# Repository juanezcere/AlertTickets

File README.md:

# AlertTickets
A PCB design to show information about tickets in BCD displays

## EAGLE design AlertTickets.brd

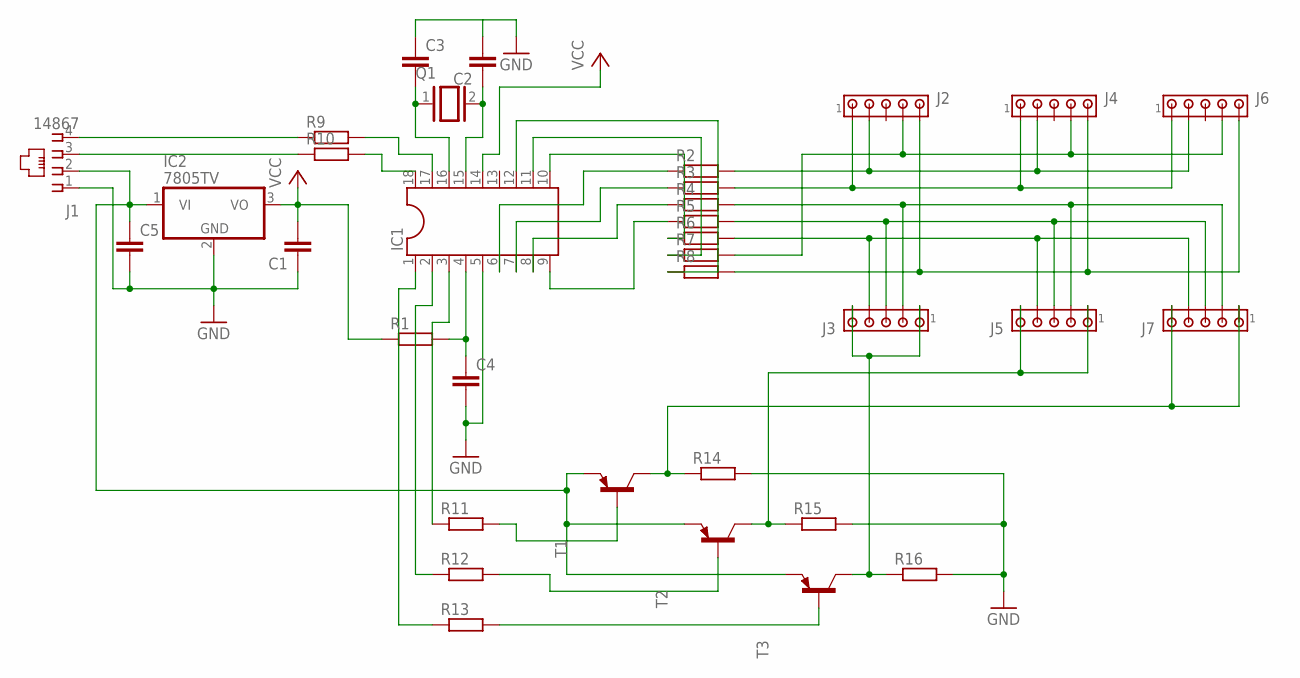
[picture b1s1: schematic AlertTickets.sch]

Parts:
C1, C2, C3, C4, C5: C-EU050-024X044; C050-024X044
IC1: DIL18
IC2: 7805TV; TO220V
J1: 14867
J2, J3, J4, J5, J6, J7: MTA05-100; 10X05MTA
Q1: XTAL/S; QS
R1, R2, R3, R4, R5, R6, R7, R8, R9, R10, R11, R12, R13, R14, R15, R16: R-EU_0207/12; 0207/12
T1, T2, T3: 2N3906-PNP-TO92-EBC; TO92-EBC

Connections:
GND: C1.1, C2.2, C3.1, C4.2, C5.2, IC1.5, IC2.2 (GND), J1.1, R14.2, R15.2, R16.2
unnamed: IC1.6, R2.1
unnamed: IC1.7, R3.1
unnamed: IC1.8, R4.1
unnamed: IC1.9, R5.1
unnamed: IC1.10, R6.1
unnamed: IC1.11, R7.1
unnamed: IC1.12, R8.1
unnamed: C4.1, IC1.4, R1.2
unnamed: C3.2, IC1.16, Q1.1
unnamed: C2.1, IC1.15, Q1.2
unnamed: C5.1, IC2.1 (VI), J1.2, T1.E, T2.E, T3.E
unnamed: J7.1, J7.5, R14.1, T1.C
unnamed: J1.4, R9.1
unnamed: J1.3, R10.1
unnamed: IC1.17, R9.2
unnamed: IC1.18, R10.2
unnamed: IC1.3, R11.1
unnamed: IC1.2, R12.1
unnamed: IC1.1, R13.1
unnamed: J5.1, J5.5, R15.1, T2.C
unnamed: J3.1, J3.5, R16.1, T3.C
unnamed: J2.2, J4.2, J6.2, R2.2
unnamed: R11.2, T1.B
unnamed: R12.2, T2.B
unnamed: R13.2, T3.B
unnamed: J2.1, J4.1, J6.1, R3.2
unnamed: J3.2, J5.2, J7.2, R4.2
unnamed: J3.3, J5.3, J7.3, R5.2
unnamed: J2.5, J4.5, J6.5, R8.2
unnamed: J2.4, J4.4, J6.4, R7.2
unnamed: J3.4, J5.4, J7.4, R6.2
VCC: C1.2, IC1.14, IC2.3 (VO), R1.1

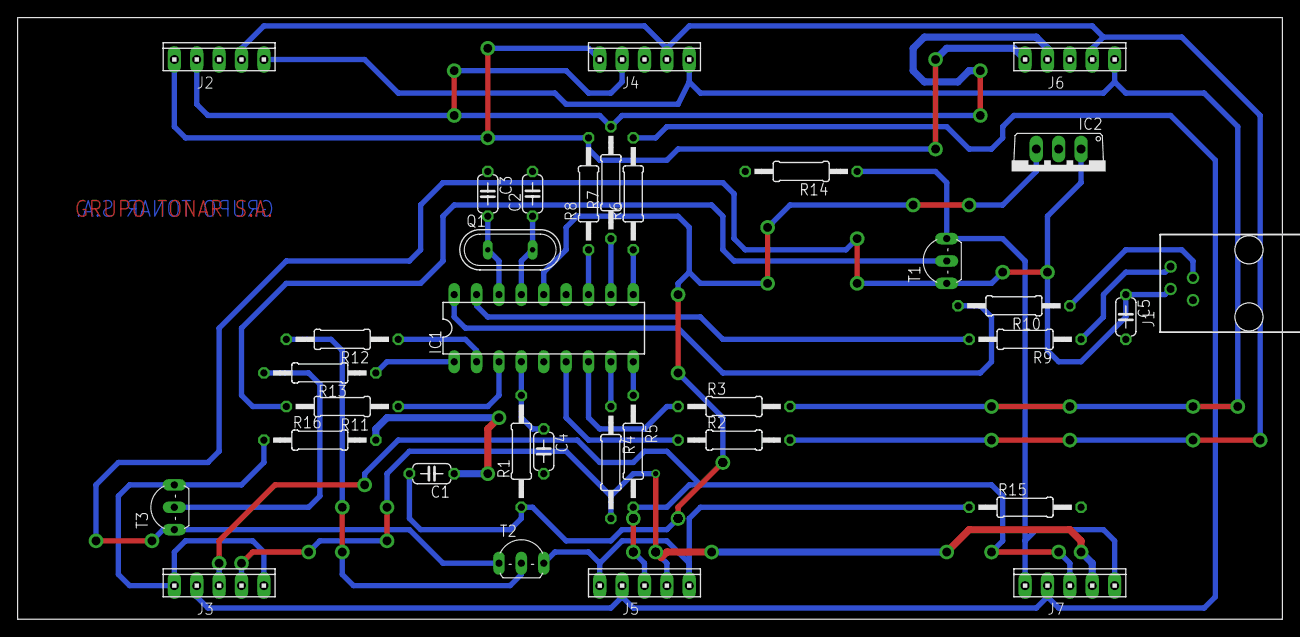
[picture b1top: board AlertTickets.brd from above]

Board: 2 copper layers, 143.5 x 68.2 mm, 34 parts (0 on the bottom side), 33 nets.

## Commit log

2022-05-22 Upload project
